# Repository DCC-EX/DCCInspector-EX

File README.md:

# DccInspector-EX

## Summary

Diagnostic/sniffer program for DCC analysis, based on an Arduino or ESP32 target.
The bit structure and packet structure are analysed and reported, and packets are decoded
and displayed in binary and also in a textual form.

On Arduino, the program produces output to the Serial port.  

On ESP32, it supports HTTP output via WiFi, and will display a reduced set of information
on an OLED display.  A button can be configured to allow the screen to be scrolled to display 
more information.  Development boards such as the Heltec Kit 32 include OLED and a button and
can be used directly.  The ESP32 will go into deep sleep mode (to preserve battery when used stand-alone) if no input 
DCC signal is detected for two minutes, it resumes when reset.

## Hardware Interface

The device may be directly connected to a DCC controller of the same I/O voltage and earth, e.g. in a
DCC++ or DCC++ EX system.  If it is used to monitor DCC signals, which are
normally bipolar 12-18V signals, an optocoupler circuit will be required.

Various circuits are discussed on the internet, but if you use a 6N137 optocoupler I 
would recommend a 1nF capacitor across the optocoupler input to stabilise the DCC input signal.  
Without this the opto-isolator may experience ringing, causing fleeting interrupts on the input 
(recorded as 'glitches' in the diagnostics).

I use a pull-up resistor of 470 ohms (labelled R3 below) on the output pin 6, connected to 5V; 
a larger resistor (even the Arduino's internal pull-up) will generally still work but may slow 
down the optocoupler.  Using the internal pull-up (~25Kohm), the rise-time on the signal is some microseconds 
in length, compared to around 200ns with a 470 (or 330) ohm pull-up.  This may be acceptable in a decoder where the
timing requirements may be relaxed, but a faster response is preferred for a diagnostic tool.

No connection is necessary to pin 7, although some versions of the circuit show a pull-up resistor here.

Strictly, the 6N137 isn't rated for the 3.3V supply used on an ESP8266 or ESP32.
I've had good results running with the circuit shown above with a 3.3V supply (replacing R3 with 330 ohm), 
but if you want to do things properly, the VCC terminal of the 6N137 should be
connected to +5V, or the optocoupler should be replaced with a 3.3V tolerant optocoupler.  In either case,
R3 should be connected to +3.3V to avoid putting too high a voltage on the ESP's input pin.

The default input pin used by the sketch depends on the target used.  For Arduino Uno and Nano, pin 8; 
for Mega, pin 49.  For the ESP8266/ESP32 it's GPIO2 (labelled D4 on the 8266 NodeMCU).

## Target Platforms

The diagnostic program supports the Arduino Uno, Nano, Mega and ESP32 particularly.

On Arduino, measurements are performed at an accuracy of 1/2 or 1/16th microsecond using Timer1 input 
capture mode, and calculation results are rounded to 1 microsecond.  

For increased compatibility with other microcontrollers, it is possible to use the micros() function for timing.
However, on an Arduino Uno/Nano/Mega this introduces up to 3us error in the micros() result, plus up to
6.5us uncertainty in the scheduling of the interrupt which samples the micros() value; consequently, the 
measured pulse length will, approximately once every millisecond, be off by up to 10us, and the rest of 
the time be up to 3us out.  This mode of operation is not recommended.

The sketch also supports the ESP8266 and ESP32.
On the ESP8266, the timing is performed using the micros() function.  Consequently, 
some inaccuracies due to interrupts are still present, of the order of 4us either way.  

The ESP32 runs in input capture mode, which works very well and potentially can support a 
measurement accuracy of around 4ns.  The sketch uses the default 12.5ns timer resolution and rounds 
the results to 1us accuracy.

## WiFi and Web Browser

On ESP8266 and ESP32, an HTTP server is provided which allows the output to be viewed from
a standard browser.  The first time the device starts, it will attempt to get WiFi credentials from the
router using WPS protocol.   Press the WPS button on the router before resetting the device, and
the device should connect to the router.  When the device is reset or started in future, it will 
connect using the same credentials by preference.

## Serial USB Output

The sketch produces output to the Serial stream, by default
once every 4 seconds.  The output statistics includes bit counts, 
bit lengths, checksum errors, packets too long, and 
time spent within the interrupt code.  Fleeting input state changes
(<= 3us) are optionally filtered and counted.  A break-down of pulse counts by 
length can also be produced, to monitor the consistency of the DCC signal.
The bit stream is validated against the specifications in NMRA S-9.1 (2020) for bit length 
and delta.  The validation can be selected through the serial monitor to be strict=0 (no validation), strict=1 
(NMRA Decoder compliance level) or strict=2 (NMRA Controller compliance level).  
The number of packets rejected due to non-compliance is recorded and displayed.

In between statistics output, received DCC packets are decoded and 
printed; duplicate throttle packets and idle packets are however not printed more than once per period.

Press '?' in the serial monitor to see help of the commands available.  The 
breakdown of pulse lengths is not displayed by default, press 'B' to enabled it.  
Likewise, the CPU statistics are not displayed by default, press 'C' to enable them.

## Example Output On Serial USB

### Example Uno Monitoring DCC++ EX 3.0.10 (5V, 6N137 Optocoupler, Main Track, Strict NMRA):
All DCC packets are within the NMRA specification
and the pulse lengths are always within 1us of the target lengths of 116us and 58us.

This demonstrates the improvements in pulse quality which were introduced in DCC++EX in 
version 3.0.5 when running on an ATmega2560 board with standard motor pins, compared to the pulse lengths
measured for the DCC++EX version 3.0.4 below.  It is achieved by using the Arduino's
hardware PWM capabilities to generate the pulse transitions; this is accurate to one clock cycle,
i.e. 1/16th of a microsecond, although the measurement accuracy is reduced slightly by the optocoupler circuit.

```
-
Bit Count/4 sec=25621 (Zeros=9134, Ones=16486), Glitches=0
Valid Packets=446, NMRA out of spec=0, Checksum Errors=0, Lost pkts=0, Long pkts=0
0 half-bit length (us): 115.9 (115-116) delta < 1
1 half-bit length (us): 57.9 (57-58) delta < 1
------ Half-bit count by length (us) -------
57	3218	0
58	13270	16490
115	2444	150
116	6690	8984
--------------------------------------------
--
Loc 3 Rev128 25         00000011 00111111 00011010
Loc 7979 Fwd128 122     11011111 00101011 00111111 11111011
-
```

### Example ESP32 Monitoring DCC++ EX 3.0.4 (5V, 6N137 Optocoupler, Main Track, Strict NMRA)
When the DCC signal is generated within interrupt handling code within the Command Station, the accuracy of 
the signal cannot be maintained to such a high accuracy.  Below, we can see that the pulse length varies over a range of around 14us.  
This would mean that some packets are outside of the NMRA specification and may be ignored by the loco decoder.
The analyser reports 81 packets as out of spec and 351 in-spec, i.e. around 20% are out of spec.  This is not 
normally a problem on a DCC layout as each packet is transmitted at least three times.  If one packet doesn't get 
through, the probability is that one of the retransmissions will!

The half-bit counts are turned off here, but CPU monitoring within the analyser is turned on.

```
-
Bit Count/4 sec=24865 (Zeros=10167, Ones=14697), Glitches=0
Valid Packets=351, NMRA out of spec=81, Checksum Errors=0, Lost pkts=0, Long pkts=0
0 half-bit length (us): 115.9 (109-122) delta < 14
1 half-bit length (us): 57.5 (51-64) delta < 14
IRC Duration (us): 2.2 (1-10),  CPU load: 27.5%
--
Loc 7552 Fwd128 33      11011101 10000000 00111111 10100010
Loc 3 Fwd128 25         00000011 00111111 10011010
-
```

### Example Uno Monitoring DCC++ Classic (5V direct connection, Main Track, Strict NMRA):
The original DCC++ Classic also uses the hardware PWM capabilities of the Arduino to generate the 
DCC pulse transitions.  This is capable of accuracy to within one clock cycle, as demonstrated in
the results below.

```
-
Bit Count/4 sec=27573 (Zeros=9881, Ones=17692), Glitches=0
Valid Packets=411, NMRA out of spec=0, Checksum Errors=0, Lost pkts=0, Long pkts=0
0 half-bit length (us): 100.0 (100-100) delta < 1
1 half-bit length (us): 58.0 (58-58) delta < 1
IRC Duration (us): 29.8 (27-39),  CPU load: 54.6%
------ Half-bit count by length (us) -------
58      17692   17692
100     9882    9882
--------------------------------------------
--
Loc 7801 Fwd128 55      11011110 01111001 00111111 10111000
Loc 2323 Fwd128 5       11001001 00010011 00111111 10000110
-
```

## Command Summary

Keyboard commands that can be sent via Serial Monitor:

```
 1 = 1s refresh time
 2 = 2s 
 3 = 4s (default)
 4 = 8s
 5 = 16s
 6 = 4 DCC packet buffer
 7 = 8
 8 = 16
 9 = 32 (default)
 0 = 64
 a = show accessory packets toggle
 l = show locomotive packets toggle
 d = show diagnostics toggle
 h = show heartbeat toggle
 b = show half-bit counts by length
 c = show cpu/irc usage in sniffer
 f = input filter toggle
 s = set NMRA compliance strictness (0=none,1=decoder,2=controller)
 ? = help (show this information)
```

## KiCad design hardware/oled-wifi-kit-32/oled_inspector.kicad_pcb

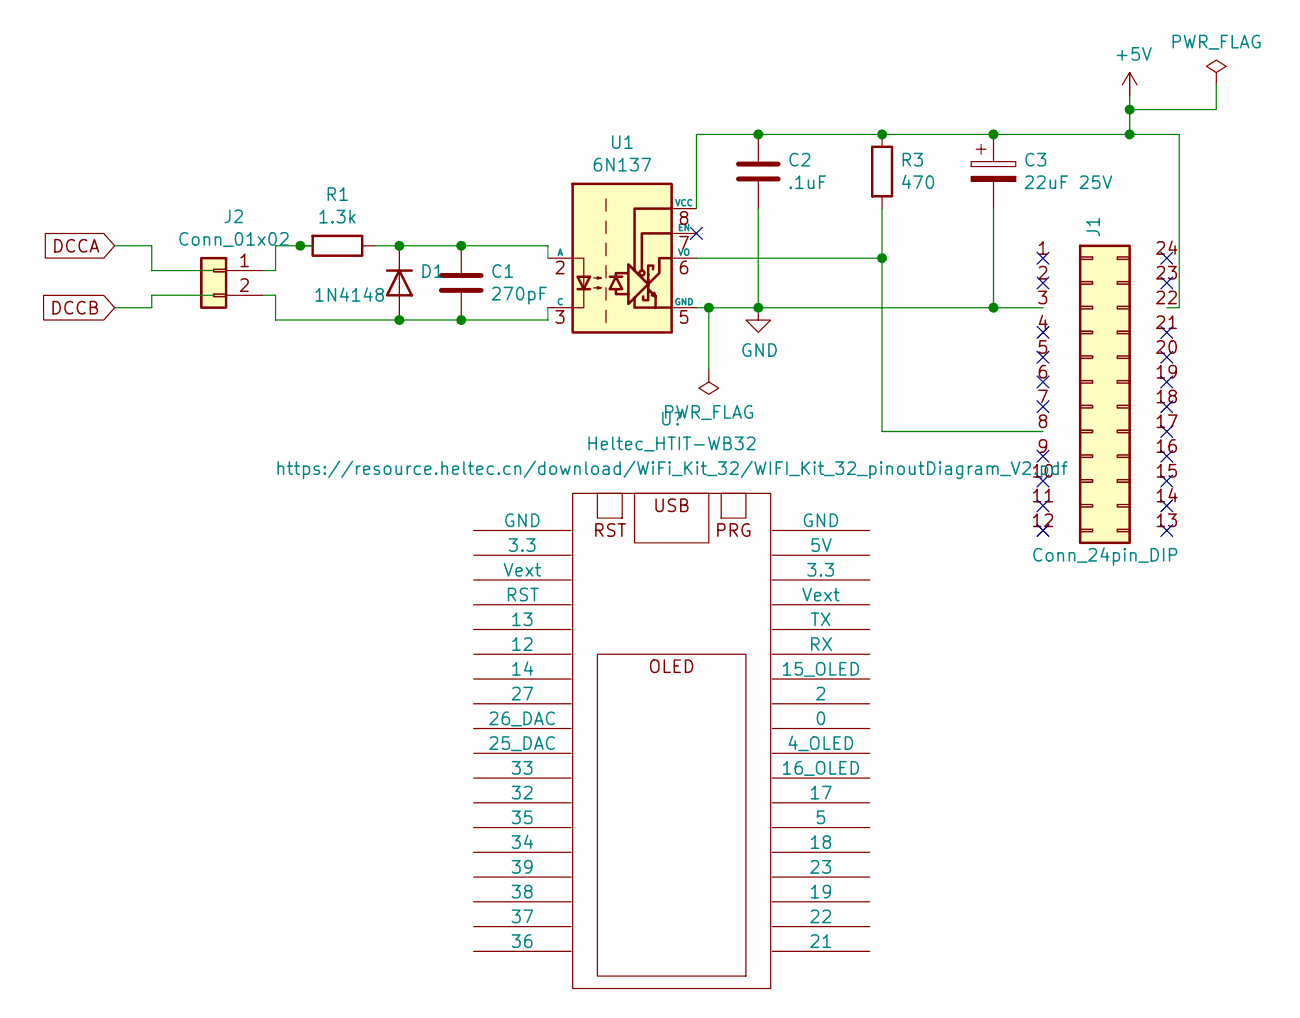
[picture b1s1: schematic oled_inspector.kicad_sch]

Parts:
C1: 270pF; CP_Radial_D8.0mm_P5.00mm
C2: .1uF; C_Disc_D3.0mm_W1.6mm_P2.50mm
C3: 22uF 25V; CP_Radial_D5.0mm_P2.00mm
D1: 1N4148; D_DO-35_SOD27_P7.62mm_Horizontal
J1: Conn_24pin_DIP; DIP-24_W15.24mm_Socket
J2: Conn_01x02; PinHeader_1x02_P2.54mm_Vertical
R1: 1.3k; R_Axial_DIN0204_L3.6mm_D1.6mm_P1.90mm_Vertical
R3: 470; R_Axial_DIN0204_L3.6mm_D1.6mm_P1.90mm_Vertical
U1: 6N137; DIP-8_W7.62mm

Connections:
+5V: C2.1, C3.1, J1.22, R3.1, U1.8 (VCC)
GND: C2.2, C3.2, J1.3, U1.5 (GND)
unnamed: C1.1, D1.1 (K), R1.1, U1.2 (A)
unnamed: C1.2, D1.2 (A), J2.2, U1.3 (C)
unnamed: J1.8, R3.2, U1.6 (VO)
unnamed: J2.1, R1.2

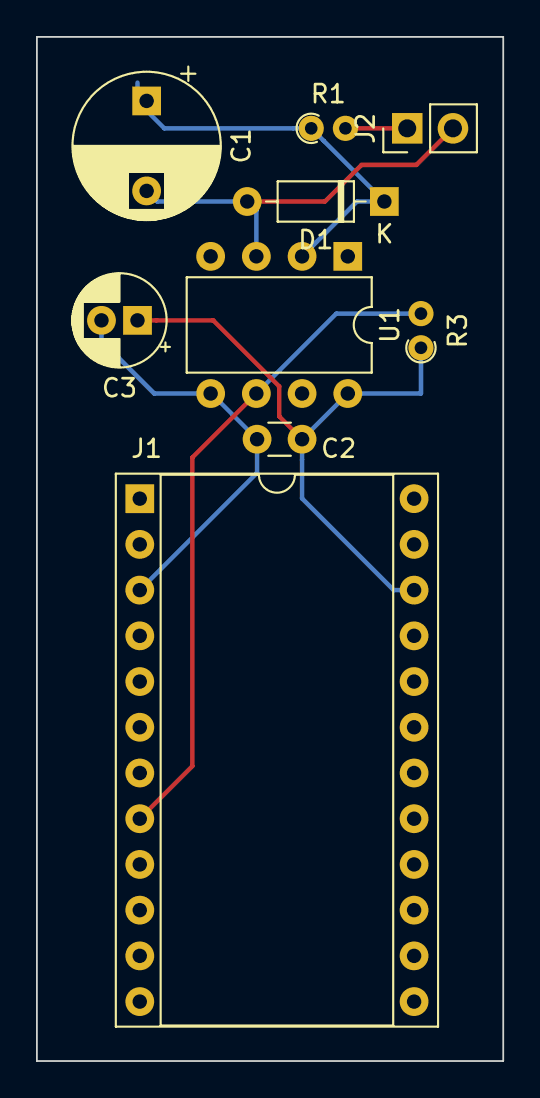
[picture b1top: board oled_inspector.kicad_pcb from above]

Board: 2 copper layers, 25.9 x 56.9 mm, 9 parts (0 on the bottom side), 6 nets.

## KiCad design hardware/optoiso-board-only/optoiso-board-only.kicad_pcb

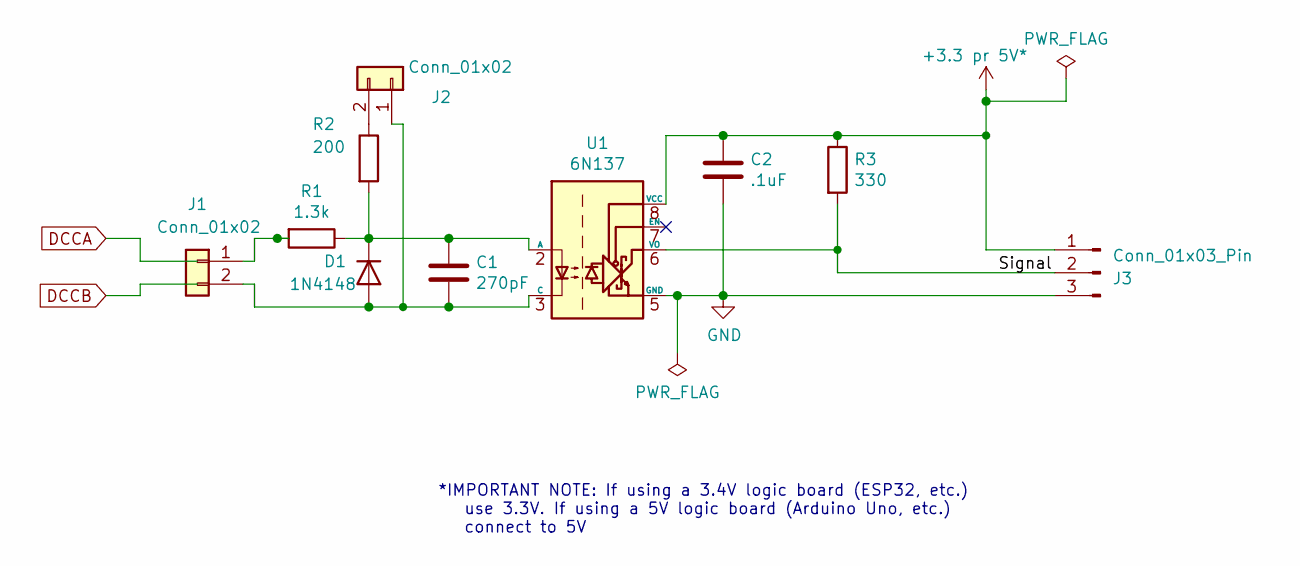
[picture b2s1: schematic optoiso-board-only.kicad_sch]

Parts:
C1: 270pF; C_Disc_D3.0mm_W2.0mm_P2.50mm
C2: .1uF; C_Disc_D3.0mm_W1.6mm_P2.50mm
D1: 1N4148; D_DO-35_SOD27_P2.54mm_Vertical_AnodeUp
J1, J2: Conn_01x02; PinHeader_1x02_P2.54mm_Vertical
J3: Conn_01x03_Pin; PinHeader_1x03_P2.54mm_Vertical
R1: 1.3k; R_Axial_DIN0204_L3.6mm_D1.6mm_P1.90mm_Vertical
R2: 200; R_Axial_DIN0204_L3.6mm_D1.6mm_P1.90mm_Vertical
R3: 330; R_Axial_DIN0204_L3.6mm_D1.6mm_P1.90mm_Vertical
U1: 6N137; DIP-8_W7.62mm

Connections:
+5V: C2.1, J3.1, R3.1, U1.8 (VCC)
GND: C2.2, J3.3, U1.5 (GND)
unnamed: C1.2, D1.2 (A), J1.2, J2.1, U1.3 (C)
unnamed: C1.1, D1.1 (K), R1.1, R2.2, U1.2 (A)
unnamed: J1.1, R1.2
unnamed: J2.2, R2.1
unnamed: J3.2, R3.2, U1.6 (VO)

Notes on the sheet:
*IMPORTANT NOTE: If using a 3.4V logic board (ESP32, etc.) use 3.3V. If using a 5V logic board (Arduino Uno, etc.) connect to 5V

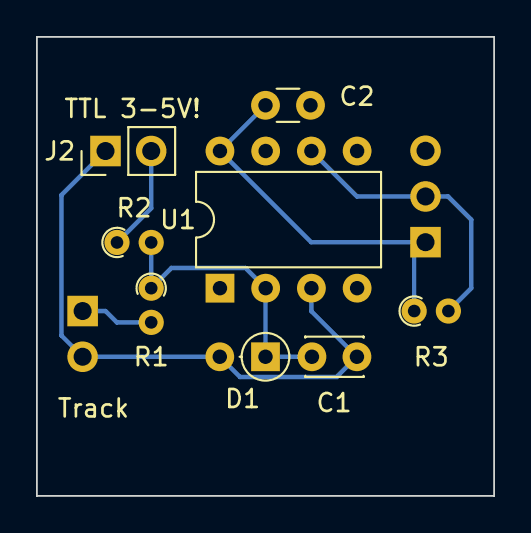
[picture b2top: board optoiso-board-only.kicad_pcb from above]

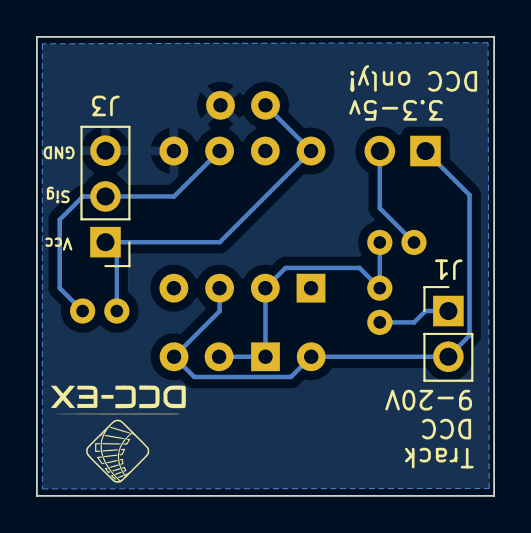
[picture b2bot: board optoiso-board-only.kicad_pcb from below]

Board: 2 copper layers, 25.4 x 25.5 mm, 10 parts (2 on the bottom side), 7 nets.

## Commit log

2021-01-16 ESP compilation.
    Update Readme, and add ESP compile support. Improve accuracy of timing.
2021-01-27 Major enhancements
    Webserver, ESP32 input capture and OLED support.
2021-01-27 Correct filename
2021-01-27 Fix L and A commands.
    Correct handling of L and A commands.
2021-01-30 Add NMRA compliance checks
    Add NMRA compliance checks;
    Inline statistics recording functions;
    Update README.
2021-02-10 Update readme opto circuit.
2021-03-13 Tidy
    Reformat source code;
    Add platformio.ini;
    Compile with all warnings;
    Change code to remove warnings.
2021-03-13 Move pictures into assets folder
2021-04-05 Update README and platformio.ini
    Update README to reflect recent improvements in DCC++EX signal quality.
    Add new nanoNew target type for nano with new 512b bootloader.
2021-04-18 Add buttons to web page for options
    Add configuration buttons to the web page.
    Tidy up structure a little.
    Fix a couple of bugs.
2021-04-18 Update HttpManager.h
    Fig compilation error
2021-04-18 Decode F29-F68 function commands
2021-04-19 Add routine to display IP address if connected in serial monitor
2021-04-19 Update DCCInspector-EX.ino
    Fix calculation of parameter in Binary State Control Instruction Long form.
2021-04-19 Update DCCInspector-EX.ino
    Add conditional compilation excludes for IP address reporting.
2021-04-27 Bug fix on calculation of binary state control instruction long form (Functions >=128).
2021-06-20 Issue #7 - change to decoded output
    For 28-step decoded packets, Forw replaced with Fwd28 and Rev replaced with Rev28 (for consistency with Fwd128 and Rev128 messages).
2021-06-22 Issue #7 - change to decoded output (#8)
    For 28-step decoded packets, Forw replaced with Fwd28 and Rev replaced with Rev28 (for consistency with Fwd128 and Rev128 messages).
2021-06-29 Fix typos in includes causing compilation errors
2021-07-08 Correct capitalisation of .h file names.
    Fix compile error on Unix platform due to mismatch in capitalisation of file names.
2021-07-08 Correct capitalisation of .h file names.
2021-07-08 Create main.yml
    Add action on checkin to do test build of sources.
2022-09-21 Add templates and project workflow
2022-11-03 Update project workflow
2022-11-03 Update workflow for forks
2023-02-19 Do not repeat identical Loco info
2023-02-19 add first commands
2023-02-19 rename printLoco to locoInfoChanged
2023-02-19 move showLoc so that it only restricts printing to sbTemp
2023-02-19 condition on result of bitRead, not on function addr
2023-02-19 nesting if/else/if/else is tricky
2023-02-20 add commands to toggle showBinary and showCommand
2023-02-20 make show* variable defaults configurable from Config.h
2023-02-22 28step command to dccex
2023-02-22 Fix speed128 step number
2023-02-24 Ignore backups folders
2023-02-24 First commit of hardware folder
2023-02-24 Add stand-alone optoisolator board project to EX-DCCInspector
2023-02-28 better function name
2023-02-28 update license text
2023-02-28 Move DecodePacket() so that isDifferntPacket matters
2023-02-28 remove isDifferntPacket and reindent whole block
2023-02-28 remove isDifferentPacket and usage of hashlist
2023-02-28 remove unused hashlist
2023-02-28 tailor serial startup
2023-03-07 Add Heltec module support
2023-03-07 Fix issue #14 HW Capture not working on Mega
2023-03-07 Fix issue #12 Compile errors
    Update code to work with ESP32 support v2.0.4 (current on Arduino and on PlatformIO).
2023-03-07 Get rid of 'undefined LED_BUILTIN' errors.
2023-03-08 Fix compilation errors on Heltek Dev Kit 32
2023-03-09 Add yet another Heltec board category
2023-03-09 replace stream.printf with sprintf
2023-03-11 Remove excluded files
2023-03-23 Bugfixes (#15)
    * Add Heltec module support
    * Fix issue #14 HW Capture not working on Mega
    * Fix issue #12 Compile errors
    Update code to work with ESP32 support v2.0.4 (current on Arduino and on PlatformIO).
    * Get rid of 'undefined LED_BUILTIN' errors.
    * Fix compilation errors on Heltek Dev Kit 32
2024-04-20 Add board information to sketch
    (for use with IniIno https://github.com/tykefcz/IniIno)
2024-04-20 Use || instead of | in #if defined for HTTP_SERVER
2024-04-20 Use || instead of | in #if defined for HTTP_SERVER
    (cherry picked from commit bfce74af40a57fb551d0f64d1cc4cc93278370ad)
2024-04-20 Disable OLED and HTTPSERVER for ARDUINO_NANO_EVERY
2024-04-20 Add AtMega0series event timer
    (copy of AtMega event timer at this point, won't compile)
2024-04-20 Change comments and author note
2024-04-20 Add fast input/output support for Arduino Nano Every
2024-04-20 Add support for Arduino Nano Every
    ...using MegaCoreX from https://github.com/MCUdude/MegaCoreX
2024-04-20 Revert "Add board information to sketch"
    Should not be included in DCC-EX PR.
    This reverts commit cfce978fbda4cd93f8da8a5fa5d0842deaf595f4.
2024-04-20 Fix comments and GPIO_PREFER_SPEED implementation
2024-04-20 Reinstate default configuration
2024-08-15 LocoTable addition (but no other changes)
2024-12-26 Add - Raspberry RP2040 support
2025-04-28 Detect RCN 5mS errors
